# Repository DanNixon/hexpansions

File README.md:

# Tildagon Hexpansions

- [Flandre Scarlet 3D printed wings](./flan-wings-3dprinted/)
- [Le Carnard de Bleu](./le-carnard-bleu/)
- [Maker Space badge](./makerspace-badge/)
- [Rabbit](./rabbit/)

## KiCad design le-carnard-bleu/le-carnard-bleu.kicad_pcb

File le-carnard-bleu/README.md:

# Le Carnard de Bleu

The magnificant piece of artwork created by Dilbert in [S2 E3 of the animated series](https://www.imdb.com/title/tt0560459/).

## Pinout

- LED red: LS E/5
- LED green: LS D/4
- LED blue: LS C/3

## Parts

- [ZD24C64A EEPROM](https://www.lcsc.com/product-detail/EEPROM_Zetta-ZD24C64A-XGMT_C2875852.html)
- [0805 4.7kOhm resistors](https://www.lcsc.com/product-detail/Chip-Resistor-Surface-Mount_VO-SCR0805J4K7_C3017854.html)
- 5mm RAGB LED

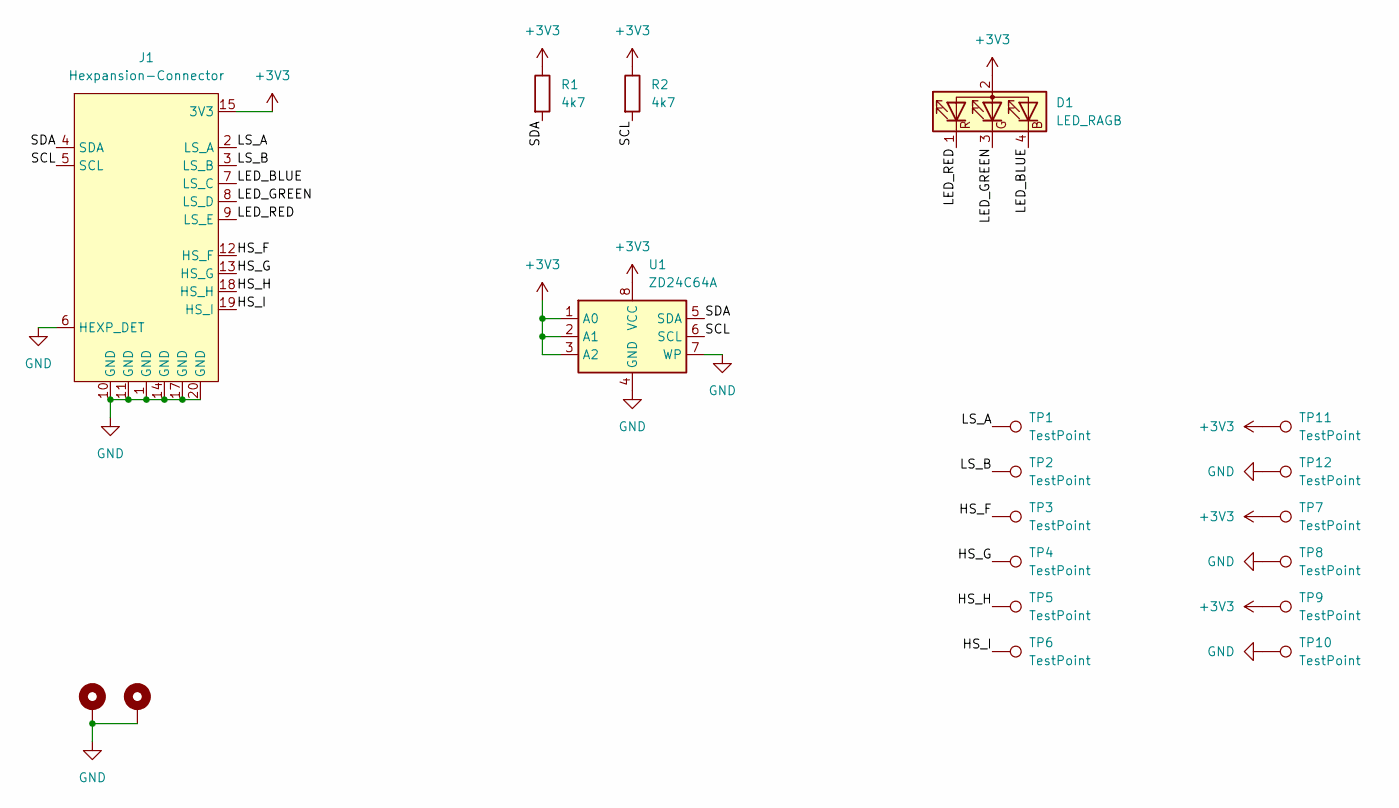
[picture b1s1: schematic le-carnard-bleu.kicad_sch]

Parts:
D1: LED_RAGB; LED_D5.0mm-4_RGB
H1, H2: MountingHole_Pad; MountingHole_2.2mm_M2_Pad_Via
J1: Hexpansion-Connector; hexpansion-edge-connector
R1, R2: 4k7; R_0805_2012Metric; LCSC C3017854
TP1, TP2, TP11, TP12: TestPoint; TestPoint_Pad_1.0x1.0mm
TP3, TP4, TP5, TP6, TP7, TP8, TP9, TP10: TestPoint; TestPoint_Pad_D1.0mm
U1: ZD24C64A; TSSOP-8_4.4x3mm_P0.65mm; LCSC C2875852

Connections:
+3V3: D1.2 (A), J1.15 (3V3), J1.16 (3V3), R1.1, R2.1, TP7.1, TP9.1, TP11.1, U1.1 (A0), U1.2 (A1), U1.3 (A2), U1.8 (VCC)
/HS_F: J1.12 (HS_F), TP3.1
/HS_G: J1.13 (HS_G), TP4.1
/HS_H: J1.18 (HS_H), TP5.1
/HS_I: J1.19 (HS_I), TP6.1
/LED_BLUE: D1.4 (BK), J1.7 (LS_C)
/LED_GREEN: D1.3 (GK), J1.8 (LS_D)
/LED_RED: D1.1 (RK), J1.9 (LS_E)
/LS_A: J1.2 (LS_A), TP1.1
/LS_B: J1.3 (LS_B), TP2.1
/SCL: J1.5 (SCL), R2.2, U1.6 (SCL)
/SDA: J1.4 (SDA), R1.2, U1.5 (SDA)
GND: H1.1, H2.1, J1.1 (GND), J1.6 (HEXP_DET), J1.10 (GND), J1.11 (GND), J1.14 (GND), J1.17 (GND), J1.20 (GND), TP8.1, TP10.1, TP12.1, U1.4 (GND), U1.7 (WP)

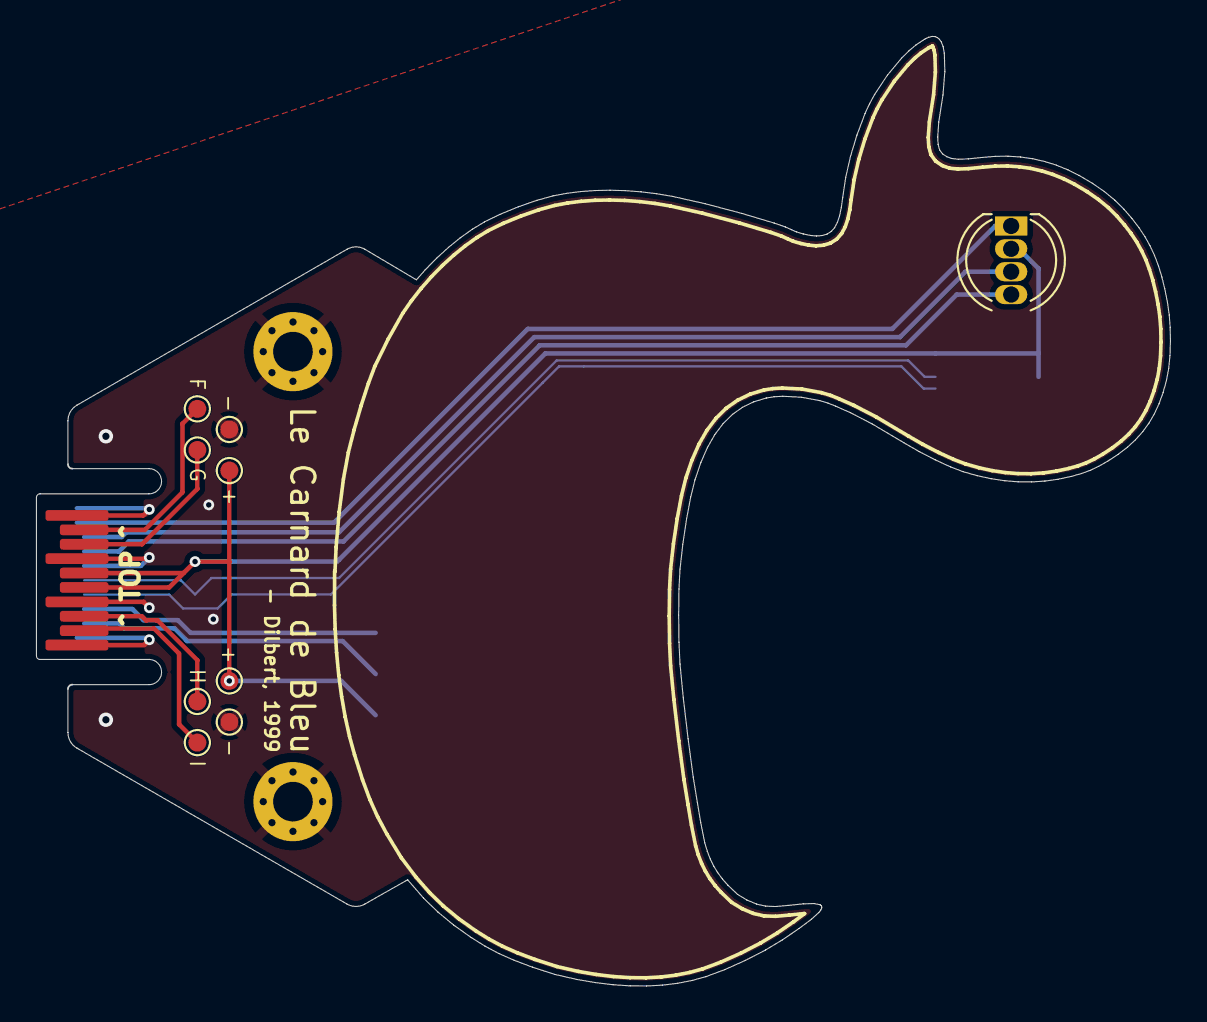
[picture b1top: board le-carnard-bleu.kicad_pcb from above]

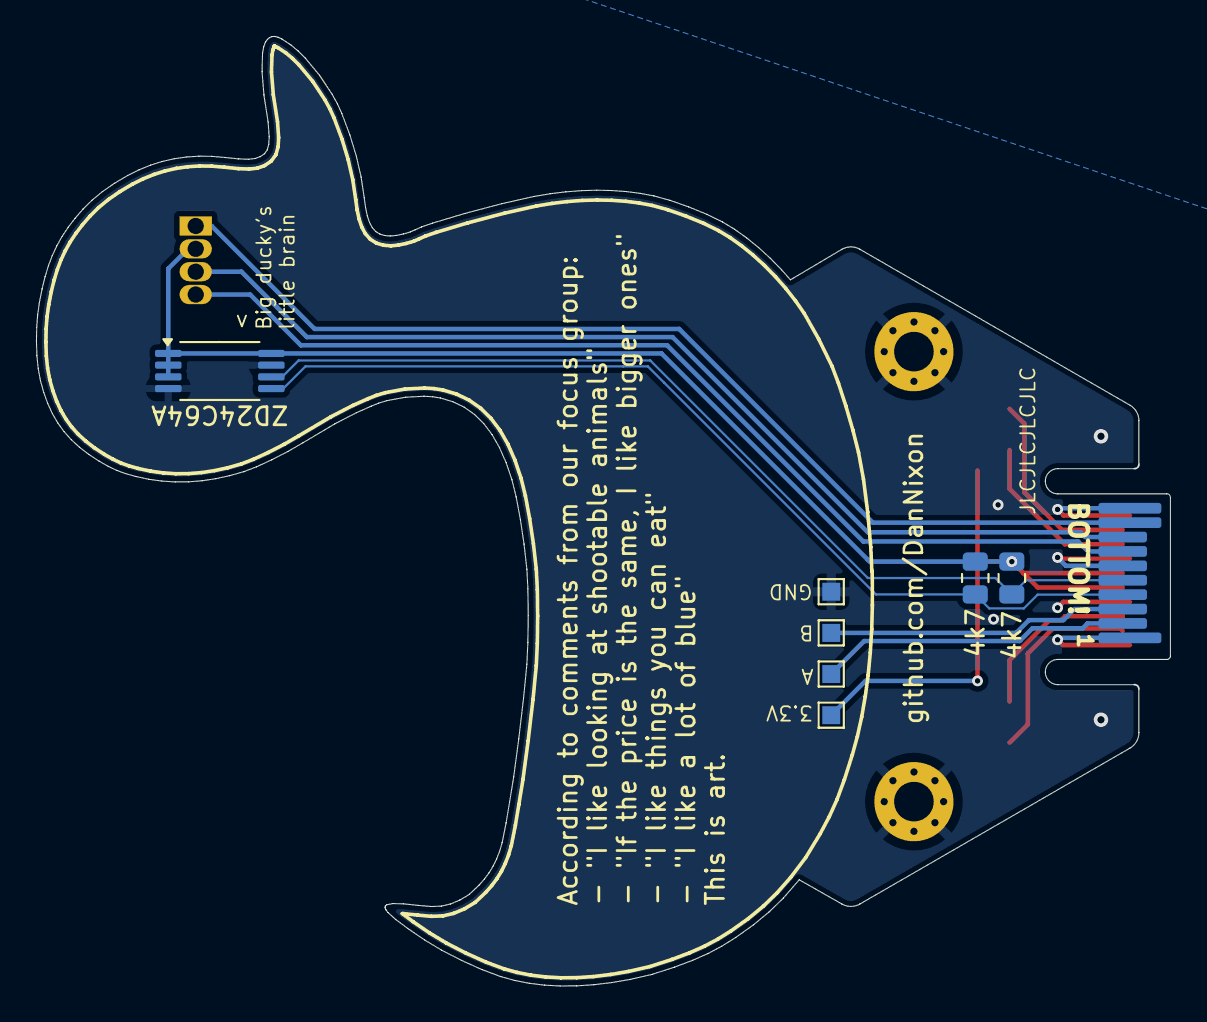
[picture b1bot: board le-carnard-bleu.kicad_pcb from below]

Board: 2 copper layers, 62.9 x 52.7 mm, 19 parts (7 on the bottom side), 13 nets.

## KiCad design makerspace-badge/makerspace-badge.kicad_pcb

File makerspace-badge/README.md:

# Maker Space badge

The [Maker Space](https://www.makerspace.org.uk/) M logo, surrounded by red LEDs with some breakouts on the bottom in the shape of the full logo.

## Pinout

Segments start at 1, with 1 being the bottom of the valley at the top of the M with subsequent segments advancing in clockwise order from there.

|M segment|Expander|Port|Pin|
|---------|--------|----|---|
|        1|       0|   0|  7|
|        2|       0|   1|  4|
|        3|       0|   1|  5|
|        4|       0|   1|  6|
|        5|       0|   1|  7|
|        6|       0|   0|  6|
|        7|       0|   0|  5|
|        8|       0|   0|  4|
|        9|       0|   0|  3|
|       10|       0|   0|  2|
|       11|       0|   0|  1|
|       12|       0|   0|  0|
|       13|       0|   1|  3|
|       14|       0|   1|  2|
|       15|       0|   1|  1|
|       16|       0|   1|  0|
|       17|       1|   0|  7|
|       18|       1|   1|  4|
|       19|       1|   0|  6|
|       20|       1|   0|  5|
|       21|       1|   0|  4|
|       22|       1|   0|  3|
|       23|       1|   0|  2|
|       24|       1|   0|  1|
|       25|       1|   0|  0|
|       26|       1|   1|  0|
|       27|       1|   1|  1|
|       28|       1|   1|  2|
|       29|       1|   1|  3|

## Parts

- [ZD24C64A EEPROM](https://www.lcsc.com/product-detail/EEPROM_Zetta-ZD24C64A-XGMT_C2875852.html)
- [AW9523BTQR LED driver](https://www.lcsc.com/product-detail/I-O-Expanders_AWINIC-Shanghai-Awinic-Tech-AW9523BTQR_C148077.html)
- [0805 4.7kOhm resistors](https://www.lcsc.com/product-detail/Chip-Resistor-Surface-Mount_VO-SCR0805J4K7_C3017854.html)
- [0603 1uF capacitors](https://www.lcsc.com/product-detail/Multilayer-Ceramic-Capacitors-MLCC-SMD-SMT_Samsung-Electro-Mechanics-CL10A105KO8NNNC_C1592.html)
- [0603 red LEDs](https://www.lcsc.com/product-detail/Light-Emitting-Diodes-LED_XINGLIGHT-XL-1608SURC-06_C965799.html)

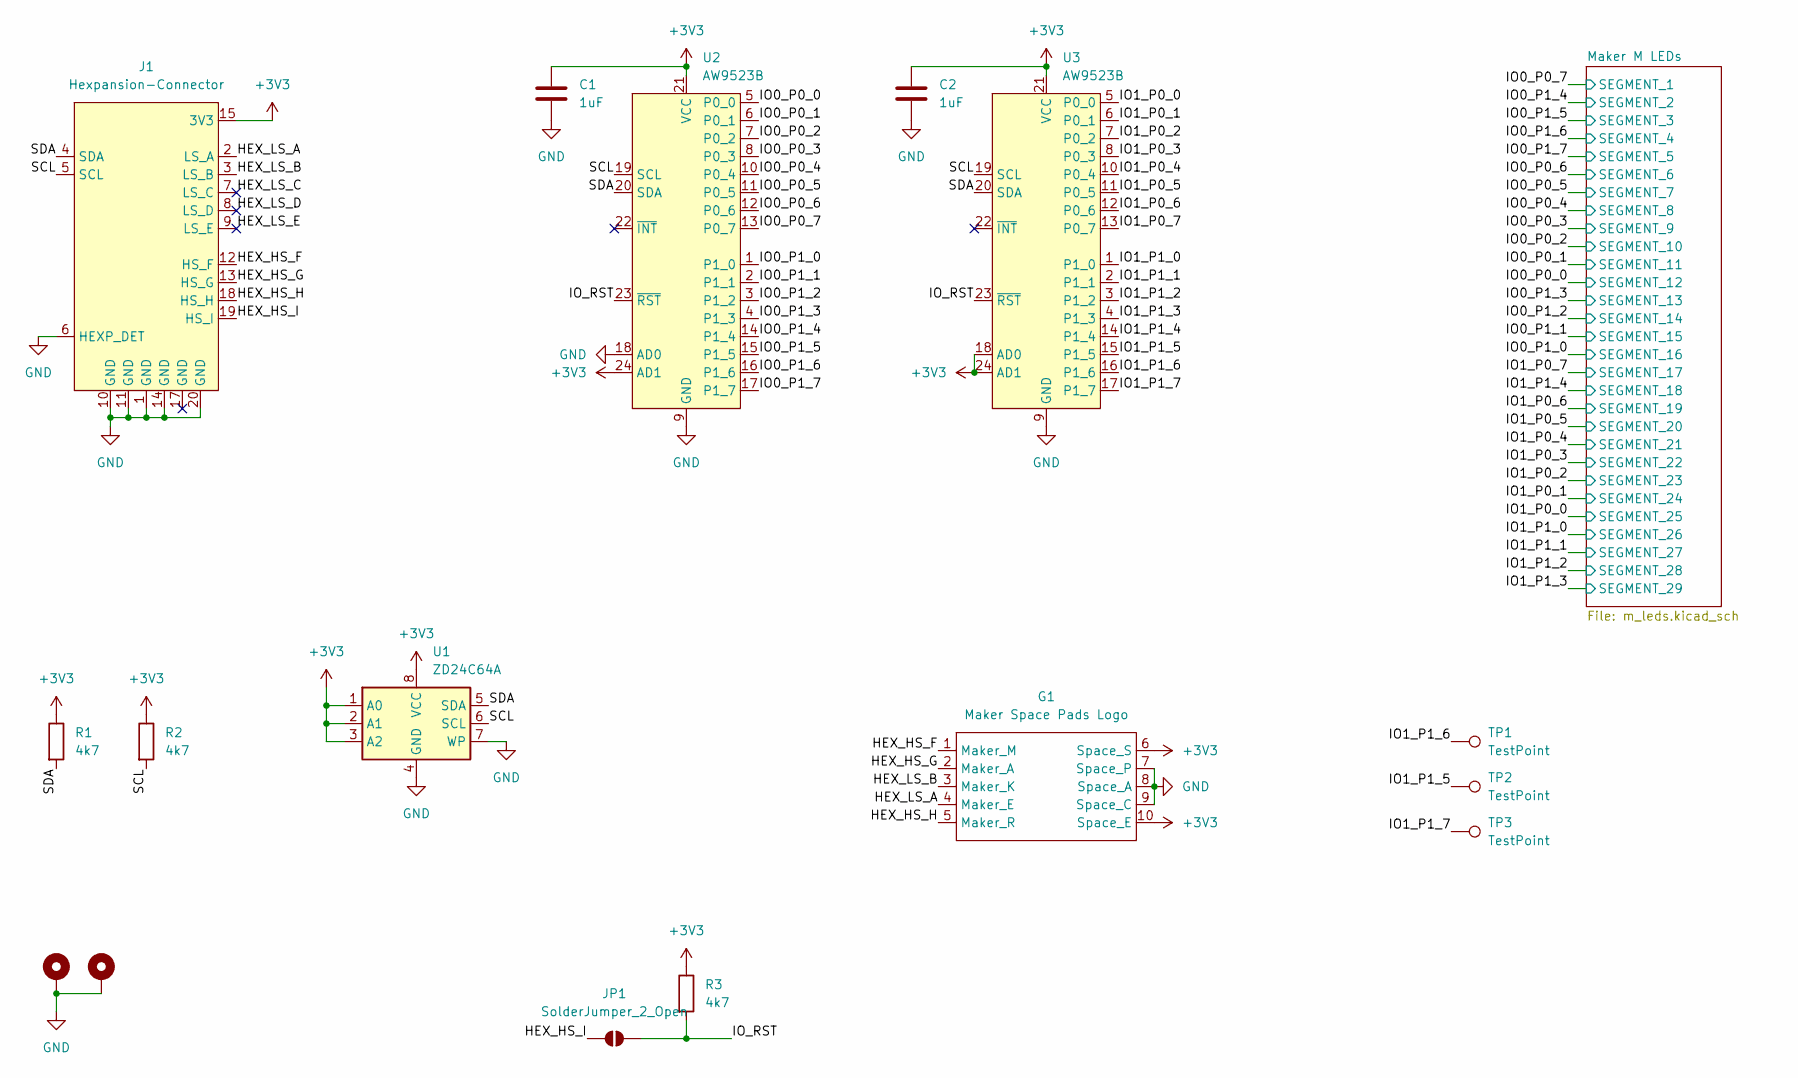
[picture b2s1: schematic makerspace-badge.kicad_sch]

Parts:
C1, C2: 1uF; C_0603_1608Metric; LCSC C1592
G1: Maker Space Pads Logo
H1, H2: MountingHole_Pad; MountingHole_2.2mm_M2_Pad_Via
J1: Hexpansion-Connector; hexpansion-edge-connector
JP1: SolderJumper_2_Open; SolderJumper-2_P1.3mm_Open_TrianglePad1.0x1.5mm
R1, R2, R3: 4k7; R_0805_2012Metric; LCSC C3017854
TP1: TestPoint; rabbit-test-pad
TP2, TP3: TestPoint; duck-test-pad
U1: ZD24C64A; TSSOP-8_4.4x3mm_P0.65mm; LCSC C2875852
U2, U3: AW9523B; QFN-24-1EP_4x4mm_P0.5mm_EP2.7x2.6mm; LCSC C148077

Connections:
+3V3: C1.1, C2.1, G1.6 (Space_S), G1.10 (Space_E), J1.15 (3V3), J1.16 (3V3), R1.1, R2.1, R3.1, U1.1 (A0), U1.2 (A1), U1.3 (A2), U1.8 (VCC), U2.21 (VCC), U2.24 (AD1), U3.18 (AD0), U3.21 (VCC), U3.24 (AD1); also elsewhere on the board
/HEX_HS_F: G1.1 (Maker_M), J1.12 (HS_F)
/HEX_HS_G: G1.2 (Maker_A), J1.13 (HS_G)
/HEX_HS_H: G1.5 (Maker_R), J1.18 (HS_H)
/HEX_HS_I: J1.19 (HS_I), JP1.1 (A)
/HEX_LS_A: G1.4 (Maker_E), J1.2 (LS_A)
/HEX_LS_B: G1.3 (Maker_K), J1.3 (LS_B)
/HEX_LS_C: J1.7 (LS_C)
/HEX_LS_D: J1.8 (LS_D)
/HEX_LS_E: J1.9 (LS_E)
/IO0_P0_0: U2.5 (P0_0); also elsewhere on the board
/IO0_P0_1: U2.6 (P0_1); also elsewhere on the board
/IO0_P0_2: U2.7 (P0_2); also elsewhere on the board
/IO0_P0_3: U2.8 (P0_3); also elsewhere on the board
/IO0_P0_4: U2.10 (P0_4); also elsewhere on the board
/IO0_P0_5: U2.11 (P0_5); also elsewhere on the board
/IO0_P0_6: U2.12 (P0_6); also elsewhere on the board
/IO0_P0_7: U2.13 (P0_7); also elsewhere on the board
/IO0_P1_0: U2.1 (P1_0); also elsewhere on the board
/IO0_P1_1: U2.2 (P1_1); also elsewhere on the board
/IO0_P1_2: U2.3 (P1_2); also elsewhere on the board
/IO0_P1_3: U2.4 (P1_3); also elsewhere on the board
/IO0_P1_4: U2.14 (P1_4); also elsewhere on the board
/IO0_P1_5: U2.15 (P1_5); also elsewhere on the board
/IO0_P1_6: U2.16 (P1_6); also elsewhere on the board
/IO0_P1_7: U2.17 (P1_7); also elsewhere on the board
/IO1_P0_0: U3.5 (P0_0); also elsewhere on the board
/IO1_P0_1: U3.6 (P0_1); also elsewhere on the board
/IO1_P0_2: U3.7 (P0_2); also elsewhere on the board
/IO1_P0_3: U3.8 (P0_3); also elsewhere on the board
/IO1_P0_4: U3.10 (P0_4); also elsewhere on the board
/IO1_P0_5: U3.11 (P0_5); also elsewhere on the board
/IO1_P0_6: U3.12 (P0_6); also elsewhere on the board
/IO1_P0_7: U3.13 (P0_7); also elsewhere on the board
/IO1_P1_0: U3.1 (P1_0); also elsewhere on the board
/IO1_P1_1: U3.2 (P1_1); also elsewhere on the board
/IO1_P1_2: U3.3 (P1_2); also elsewhere on the board
/IO1_P1_3: U3.4 (P1_3); also elsewhere on the board
/IO1_P1_4: U3.14 (P1_4); also elsewhere on the board
/IO1_P1_5: TP2.1, U3.15 (P1_5)
/IO1_P1_6: TP1.1, U3.16 (P1_6)
/IO1_P1_7: TP3.1, U3.17 (P1_7)
/IO_RST: JP1.2 (B), R3.2, U2.23 (~RST), U3.23 (~RST)
/SCL: J1.5 (SCL), R2.2, U1.6 (SCL), U2.19 (SCL), U3.19 (SCL)
/SDA: J1.4 (SDA), R1.2, U1.5 (SDA), U2.20 (SDA), U3.20 (SDA)
GND: C1.2, C2.2, G1.7 (Space_P), G1.8 (Space_A), G1.9 (Space_C), H1.1, H2.1, J1.1 (GND), J1.6 (HEXP_DET), J1.10 (GND), J1.11 (GND), J1.14 (GND), J1.20 (GND), U1.4 (GND), U1.7 (WP), U2.9 (GND), U2.18 (AD0), U2.25 (GND), U3.9 (GND), U3.25 (GND)

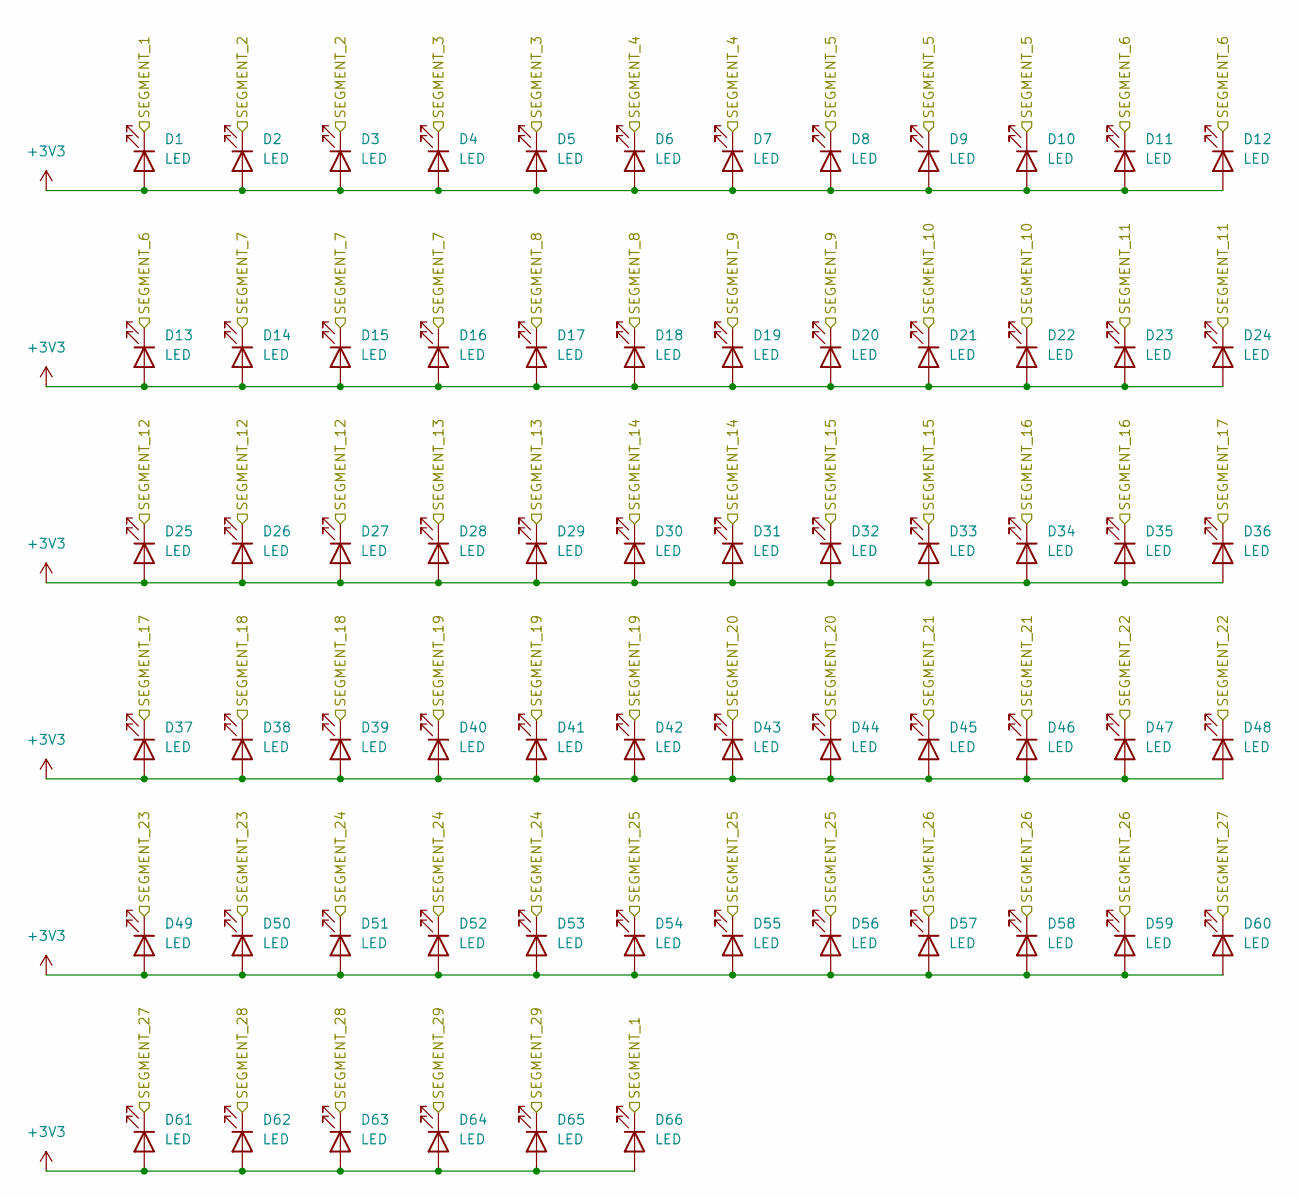
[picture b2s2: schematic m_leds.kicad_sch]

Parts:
D1, D2, D3, D4, D5, D6, D7, D8, D9, D10, D11, D12, D13, D14, D15, D16, D17, D18, D19, D20, D21, D22, D23, D24, D25, D26, D27, D28, D29, D30, D31, D32, D33, D34, D35, D36, D37, D38, D39, D40, D41, D42, D43, D44, D45, D46, D47, D48, D49, D50, D51, D52, D53, D54, D55, D56, D57, D58, D59, D60, D61, D62, D63, D64, D65, D66: LED; LED_0603_1608Metric_NoSilkscreen; LCSC C965799

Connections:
+3V3: D1.2 (A), D2.2 (A), D3.2 (A), D4.2 (A), D5.2 (A), D6.2 (A), D7.2 (A), D8.2 (A), D9.2 (A), D10.2 (A), D11.2 (A), D12.2 (A), D13.2 (A), D14.2 (A), D15.2 (A), D16.2 (A), D17.2 (A), D18.2 (A), D19.2 (A), D20.2 (A), D21.2 (A), D22.2 (A), D23.2 (A), D24.2 (A), D25.2 (A), D26.2 (A), D27.2 (A), D28.2 (A), D29.2 (A), D30.2 (A), D31.2 (A), D32.2 (A), D33.2 (A), D34.2 (A), D35.2 (A), D36.2 (A), D37.2 (A), D38.2 (A), D39.2 (A), D40.2 (A), D41.2 (A), D42.2 (A), D43.2 (A), D44.2 (A), D45.2 (A), D46.2 (A), D47.2 (A), D48.2 (A), D49.2 (A), D50.2 (A), D51.2 (A), D52.2 (A), D53.2 (A), D54.2 (A), D55.2 (A), D56.2 (A), D57.2 (A), D58.2 (A), D59.2 (A), D60.2 (A), D61.2 (A), D62.2 (A), D63.2 (A), D64.2 (A), D65.2 (A), D66.2 (A); also elsewhere on the board
/IO0_P0_0: D25.1 (K), D26.1 (K), D27.1 (K); also elsewhere on the board
/IO0_P0_1: D23.1 (K), D24.1 (K); also elsewhere on the board
/IO0_P0_2: D21.1 (K), D22.1 (K); also elsewhere on the board
/IO0_P0_3: D19.1 (K), D20.1 (K); also elsewhere on the board
/IO0_P0_4: D17.1 (K), D18.1 (K); also elsewhere on the board
/IO0_P0_5: D14.1 (K), D15.1 (K), D16.1 (K); also elsewhere on the board
/IO0_P0_6: D11.1 (K), D12.1 (K), D13.1 (K); also elsewhere on the board
/IO0_P0_7: D1.1 (K), D66.1 (K); also elsewhere on the board
/IO0_P1_0: D34.1 (K), D35.1 (K); also elsewhere on the board
/IO0_P1_1: D32.1 (K), D33.1 (K); also elsewhere on the board
/IO0_P1_2: D30.1 (K), D31.1 (K); also elsewhere on the board
/IO0_P1_3: D28.1 (K), D29.1 (K); also elsewhere on the board
/IO0_P1_4: D2.1 (K), D3.1 (K); also elsewhere on the board
/IO0_P1_5: D4.1 (K), D5.1 (K); also elsewhere on the board
/IO0_P1_6: D6.1 (K), D7.1 (K); also elsewhere on the board
/IO0_P1_7: D8.1 (K), D9.1 (K), D10.1 (K); also elsewhere on the board
/IO1_P0_0: D54.1 (K), D55.1 (K), D56.1 (K); also elsewhere on the board
/IO1_P0_1: D51.1 (K), D52.1 (K), D53.1 (K); also elsewhere on the board
/IO1_P0_2: D49.1 (K), D50.1 (K); also elsewhere on the board
/IO1_P0_3: D47.1 (K), D48.1 (K); also elsewhere on the board
/IO1_P0_4: D45.1 (K), D46.1 (K); also elsewhere on the board
/IO1_P0_5: D43.1 (K), D44.1 (K); also elsewhere on the board
/IO1_P0_6: D40.1 (K), D41.1 (K), D42.1 (K); also elsewhere on the board
/IO1_P0_7: D36.1 (K), D37.1 (K); also elsewhere on the board
/IO1_P1_0: D57.1 (K), D58.1 (K), D59.1 (K); also elsewhere on the board
/IO1_P1_1: D60.1 (K), D61.1 (K); also elsewhere on the board
/IO1_P1_2: D62.1 (K), D63.1 (K); also elsewhere on the board
/IO1_P1_3: D64.1 (K), D65.1 (K); also elsewhere on the board
/IO1_P1_4: D38.1 (K), D39.1 (K); also elsewhere on the board

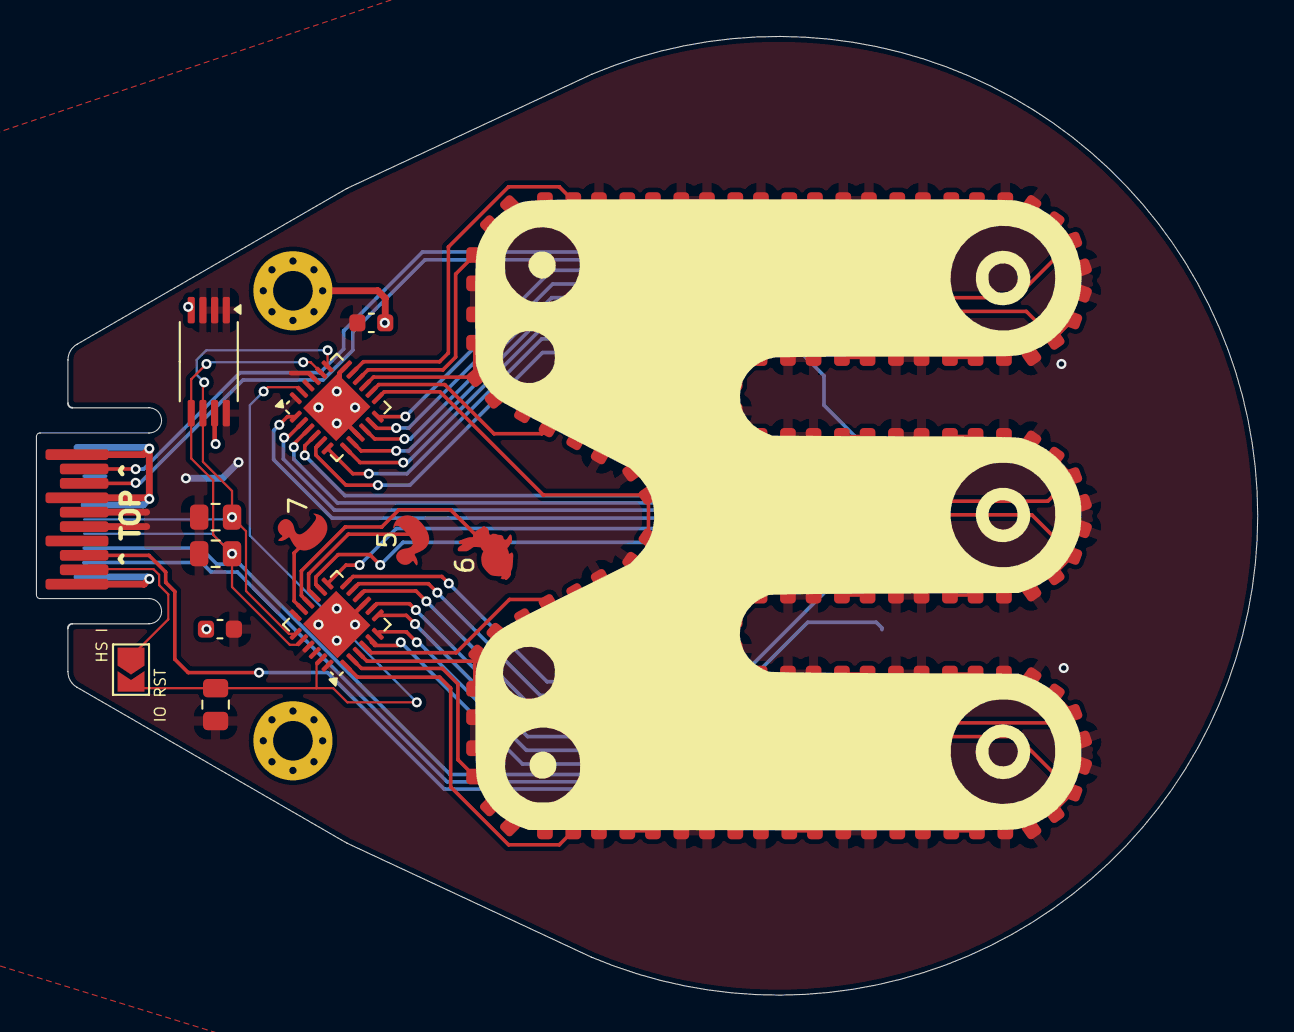
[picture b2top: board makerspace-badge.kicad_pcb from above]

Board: 2 copper layers, 67.8 x 53.2 mm, 82 parts (1 on the bottom side), 43 nets.

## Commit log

2024-04-20 Add common lib
2024-04-20 Maker Space badge, revision A
2024-04-20 Rabbit, revision A
2024-04-20 Le Carnard de Bleu, revision A
2024-04-20 Ferris, WIP
2024-04-20 fixup! Ferris, WIP
2024-04-20 Maker Space badge, revision B
2024-04-20 Rabbit, Revision B
    Fix back side silkscreen
2024-04-20 Le Carnard de Bleu, Revision B
    Fix silkscreen issues
2024-04-22 Add FUNDING.yml
2024-04-29 Add LED pinouts
2024-05-14 Add MS hexpansion pinout
2024-05-14 Add note on segment positions and ordering on MS hex
2024-05-27 Flandre Scarlet 3D printed wings
2024-05-31 Rotate hexpansion adapter on Flan Wings by 30 degrees
    Fixes #2
2024-07-05 Add maker space hexpansion app (#3)
    * Add maker space hexpansion app
    * Add license
2025-09-01 Numerical pinouts
